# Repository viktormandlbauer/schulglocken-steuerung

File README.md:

# schulglocken-steuerung

## Libraries

* [Time Library](https://github.com/PaulStoffregen/Time)
* [RTC Library](https://github.com/adafruit/RTClib)
* [Ethernet Library](https://github.com/njh/EtherCard/)
* [Graphics Library](https://learn.adafruit.com/adafruit-gfx-graphics-library)
* [Display Documentation](https://www.waveshare.com/wiki/4inch_TFT_Touch_Shield)
* [Arduino Reference](https://reference.arduino.cc/reference/en/)
* [Touch Driver](https://github.com/PaulStoffregen/XPT2046_Touchscreen/blob/master/examples/TouchTestIRQ/TouchTestIRQ.ino)

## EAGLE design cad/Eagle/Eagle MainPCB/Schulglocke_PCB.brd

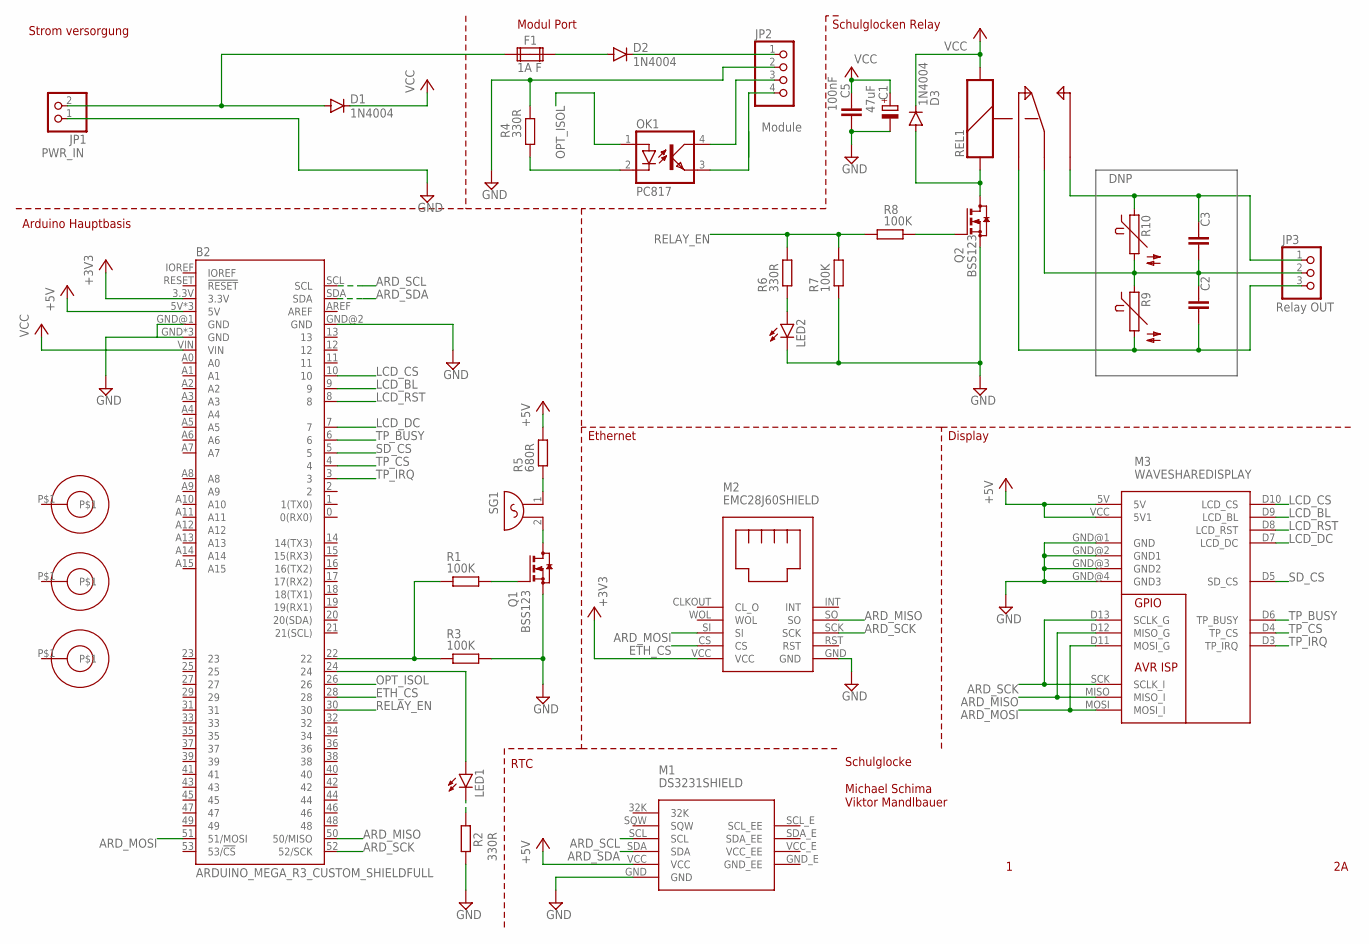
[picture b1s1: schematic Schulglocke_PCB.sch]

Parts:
B2: ARDUINO_MEGA_R3_CUSTOM_SHIELDFULL; ARDUINO_MEGA_NO_SILK
C1: 47uF; 153CLV-0605
C2, C3: DNP; C102-064X133
C5: 100nF; C1206K
D1, D2, D3: 1N4004; DO41-10
F1: 1A F; FUSE1
JP1: PINHD-1X2; 1X02
JP2: PINHD-1X4; 1X04
JP3: PINHD-1X3; 1X03
LED1, LED2: LED3MM
M1: DS3231SHIELD; DS3231_F
M2: EMC28J60SHIELD; EMC_F
M3: WAVESHAREDISPLAY; ARDUINO_R3_NO_HOLES
OK1: PC817; DIL04
Q1, Q2: BSS123; SOT23
R1, R3, R7, R8: 100K; M1206
R2, R4, R6: 330R; M1206
R5: 680R; M1206
R9, R10: P593
REL1: REL-5PIN
SG1: F/HGP
U$1, U$2, U$3: MOUNTPOINT3.3MM; MOUNT_POINT_3.3MM

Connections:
+3V3: B2.3.3V, M2.VCC
+5V: B2.5V, B2.5V@1 (5V), B2.5V@2 (5V), M1.VCC, M3.5V, M3.VCC (5V1), R5.2
ARD_MISO: B2.50 (50/MISO), M2.SO, M3.D12 (MISO_G), M3.MISO (MISO_I)
ARD_MOSI: B2.51 (51/MOSI), M2.SI, M3.D11 (MOSI_G), M3.MOSI (MOSI_I)
ARD_SCK: B2.52 (52/SCK), M2.SCK, M3.D13 (SCLK_G), M3.SCK (SCLK_I)
ARD_SCL: B2.SCL, M1.SCL
ARD_SDA: B2.SDA, M1.SDA
ETH_CS: B2.28, M2.CS
GND: B2.GND, B2.GND@1 (GND), B2.GND@2 (GND), B2.GND@3 (GND), B2.GND@4 (GND), C1.-, C5.2, JP1.1, JP2.2, LED2.K (C), M1.GND, M2.GND, M3.GND@1 (GND), M3.GND@2 (GND1), M3.GND@3 (GND2), M3.GND@4 (GND3), Q1.2 (S), Q2.2 (S), R2.2, R3.2, R4.2, R7.2
LCD_BL: B2.9, M3.D9 (LCD_BL)
LCD_CS: B2.10, M3.D10 (LCD_CS)
LCD_DC: B2.7, M3.D7 (LCD_DC)
LCD_RST: B2.8, M3.D8 (LCD_RST)
unnamed: C2.1, C3.2, JP3.2, R9.1, R10.2, REL1.C
unnamed: C3.1, JP3.1, R10.1, REL1.O
unnamed: C2.2, JP3.3, R9.2, REL1.S
unnamed: D2.A, F1.2A
unnamed: D2.C, JP2.1
unnamed: JP2.3, OK1.4 (COL)
unnamed: JP2.4, OK1.3 (EMIT)
unnamed: D1.A, F1.1A, JP1.2
unnamed: D3.A, Q2.3 (D), REL1.S1
unnamed: B2.24, LED1.A
unnamed: LED2.A, R6.1
unnamed: R5.1, SG1.1
unnamed: Q1.3 (D), SG1.2
unnamed: B2.22, R1.2, R3.1
unnamed: Q1.1 (G), R1.1
unnamed: OK1.2 (C), R4.1
unnamed: Q2.1 (G), R8.1
unnamed: LED1.K (C), R2.1
OPT_ISOL: B2.26, OK1.1 (A)
RELAY_EN: B2.30, R6.2, R7.1, R8.2
SD_CS: B2.5, M3.D5 (SD_CS)
TP_BUSY: B2.6, M3.D6 (TP_BUSY)
TP_CS: B2.4, M3.D4 (TP_CS)
TP_IRQ: B2.3, M3.D3 (TP_IRQ)
VCC: B2.VIN, C1.+, C5.1, D1.C, D3.C, REL1.S2

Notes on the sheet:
Schulglocke Michael Schima Viktor Mandlbauer
Arduino Hauptbasis
Strom versorgung
Modul Port
Display
Ethernet
RTC
Schulglocken Relay
DNP
PWR_IN
Module
Relay OUT

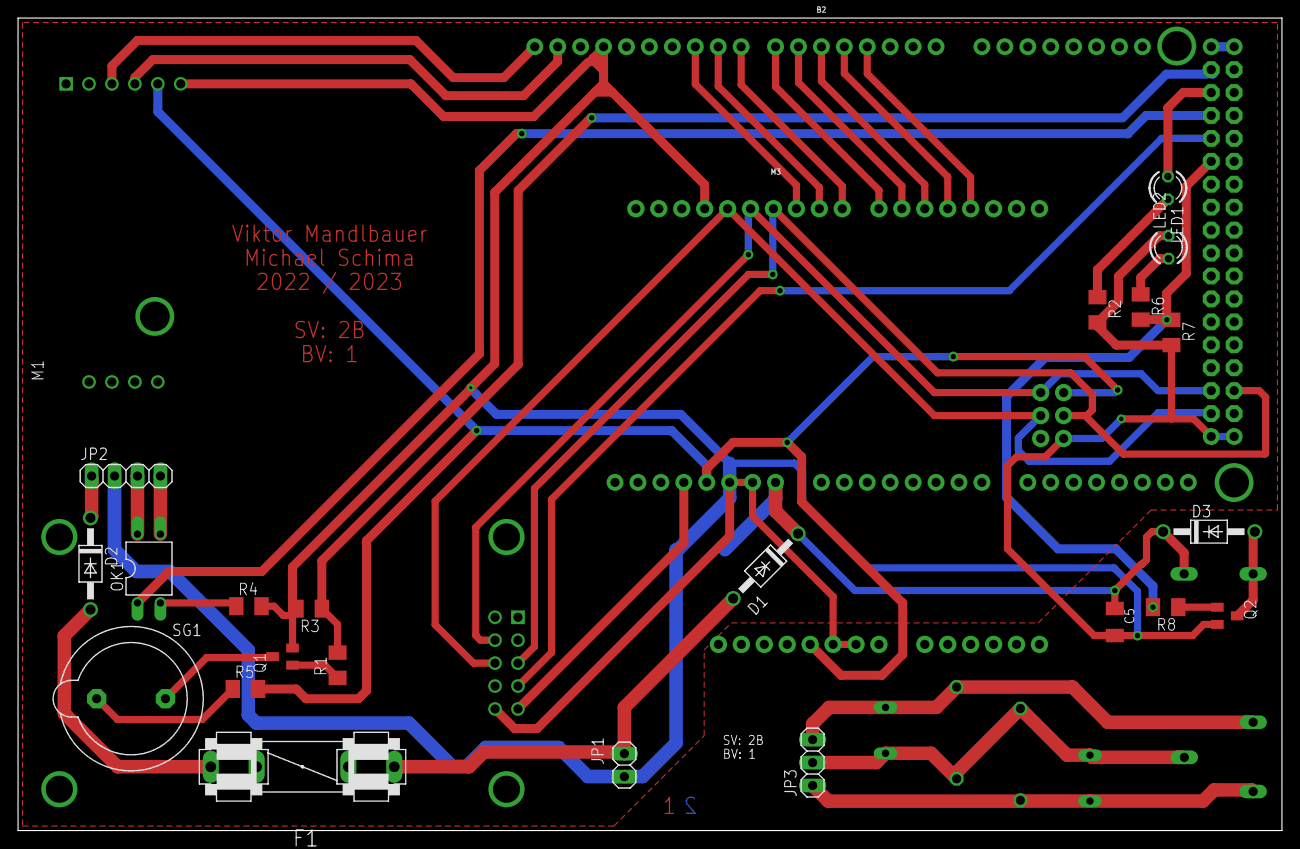
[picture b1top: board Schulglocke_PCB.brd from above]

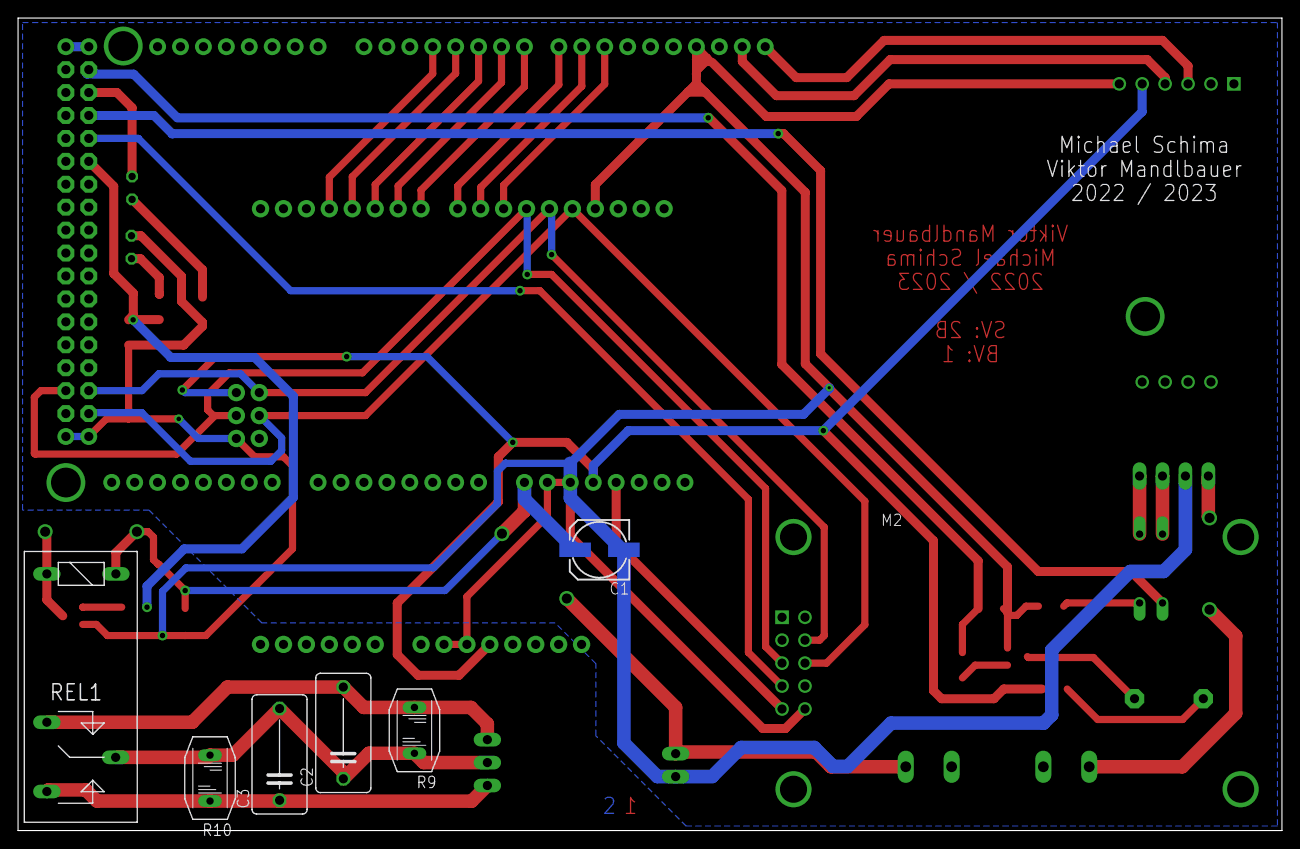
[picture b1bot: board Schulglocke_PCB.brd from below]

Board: 2 copper layers, 140.0 x 90.0 mm, 35 parts (7 on the bottom side), 38 nets.

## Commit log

2022-09-26 Initial empty platformio project
2022-09-26 Datashet DS3231S
2022-10-01 Added Display library to project
2022-10-01 Added display libs
2022-10-01 display library exampels and src files
2022-10-01 Added time libraries
2022-10-01 Added network libraries
2022-10-01 Reset main branch
2022-10-02 erster schaltplan mit allen esenziellen bauteilen
2022-10-02 Added new display lib
2022-10-10 Working ethercard library
2022-10-10 Includes
2022-10-10 Simple button
2022-10-10 Added Img2Code for bitmap conversion
2022-10-11 Print Text
2022-10-11 display time
2022-10-12 Header files
2022-10-13 Network class
2022-10-15 Network class implementation for header filer
2022-10-15 get_time_string implementation
2022-10-15 New draw time
2022-10-16 HTTP Response
2022-10-18 Namespaces GUI, Network & Time
2022-11-10 New network
2022-11-10 Working website example - still testing shield
2022-11-13 Website mit Zeitanzeige
2022-11-14 Timequeue
2022-11-24 Removed vscode dir
2022-11-24 Switching to another branch
2022-11-27 erster display test
2022-11-27 fix arduino ser port
2022-11-28 versuchter zurück pfeil
2022-11-28 zurück pfeil
2022-12-05 Updated Time
2022-12-12 First storage definition
2022-12-12 Cleanup time
2022-12-12 Deleted .vscode
2022-12-23 small changes
2022-12-23 get_time as char array, add_alarm, remove_alarm
2023-01-06 More time functionality - add alarms, remove alarms, time strings
2023-01-08 Implementierung des simplen Läutens zu definierten Alarmzeiten
2023-01-08 Interrupt routine for alarms and different alarm types
2023-01-09 Ready for storage
2023-01-09 Small change
2023-01-09 Storage for alarms
2023-01-15 Saving alarms and reading them from storage
2023-01-15 Storage for network config and definition file for debug and storage settings
2023-01-15 Updated definitions
2023-01-15 Moved MAC Address definition into DEFINTION.h file
2023-01-15 Changed definitions file
2023-01-15 Beginning of GUI navigation logic
2023-01-16 Buttons
2023-01-17 More GUI interaction
2023-01-19 platformio.ini
2023-01-20 Fixed print bug
2023-01-20 Changed HH:MM:SS get_timestring function
2023-01-22 neuer schaltplan jetzt in eagle
2023-01-22 demo gehäuse
2023-01-22 correct folder name
2023-01-22 korrektur ueberhang
2023-01-23 Unused branches
2023-01-23 Storage for network and arduino mega adaption
2023-01-31 Alarm GUI mit scrollen
2023-02-11 Display Actions
2023-02-12 Fixed GUI
2023-02-12 GUI - draw numeric keyboard
2023-02-13 GUI - Keyboard for alarm setting
2023-02-13 Alarme konfigurierbar. ToDo: Funktion für neuen Alarm fixen
2023-02-14 Fixed refreshing with new alarm
2023-02-14 some changes for structs
2023-02-14 Finished struct alarms and add new alarms
2023-02-15 definitions for return codes for better code readability
2023-02-15 Adding and modifying alarms works fine
2023-02-16 Modifying alarms via GUI and using persistent storage
2023-02-16 Current time
2023-02-18 Display current time
2023-02-18 Modifying time in GUI and syncing rtc module
2023-02-19 korekte bauteile
2023-02-19 neue numerierung
2023-03-09 before change
2023-03-09 leiterplatte plaziert
2023-03-13 mit traces noch ohne montagelöcher und ohne anpassung footprints
2023-03-16 added drill holes
2023-03-23 changed ds clock layou
2023-03-26 final version
2023-03-26 added pdf with dimentions & docu
2023-03-26 flipped buzzer
2023-03-27 Display - Show current network settings
2023-04-06 TODO: Timezones and NTP
2023-04-06 Working Timesync
2023-04-06 Syncing time with interval (RTC/NTP)
2023-04-08 Fixed switch statement and added persistent NTP configuation (in progress)
2023-04-09 DHCP Configuration - for some reason the TimeSync functionality from TimeLib.h breaks the DHCP setup...
2023-04-09 Bugfix - DHCP and NTP
2023-04-11 Pin definitions
2023-04-11 Added touch driver library
2023-04-11 Added touchscreen driver
2023-04-12 GUI IP config
2023-04-16 Using touchscreen interrupt
2023-04-18 GUI - default menu
2023-04-18 Default menu - todo: upcoming day exceptions
2023-04-27 Date-Exception menus
2023-04-30 Gehaeuse
2023-04-30 korrigiere lan abd
2023-04-30 clean freecad prj
2023-04-30 2 case versions
2023-05-01 GUI: Add date exception
2023-05-07 Adding persistent alarm exceptions
2023-05-07 GUI - Setting persistent weekday exceptions
2023-05-15 sync
2023-05-15 removed documents
2023-05-15 flyer 1
2023-05-17 data
2023-05-18 Working date- and weekexception. Configurable datetime
2023-05-21 Static IP configuration
2023-05-22 Bugfix Ethernet - caused by mac address in PROGMEM
2023-05-26 Enviroment settings for arduino uno and mega
2023-05-28 Documentation and refactoring
2023-05-28 Documentation TimeSync
2023-05-28 Documentation
2023-05-29 Documentation Storage Headerfile
2023-05-29 Documentation Network
2023-05-29 Documentation GUI
2023-05-30 fixed a name
2023-05-30 freecad cad files
2023-06-12 Changed default menu to main menu
